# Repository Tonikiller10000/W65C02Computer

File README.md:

# W65C02Computer

### Description:
This is an 8 bit computer made with the W65C02 processor inspired by Ben Eater.
After board arrival, I will test the clk maximum speed (20MHz), some methods to write into ROM (take\`s too much time to write to it) and some other experiments with this design, beeing made mostly after the Ben Eater\`s original design.

### Features:
 - 8 bit processor
 - 1-10MHz CLK
 - 16K RAM
 - 32K ROM
 - USB C Powered
 - Serial interface
 - Multiple GPIO

<table>
  <tr>
    <td></td>
    <td></td>
  </tr>
 </table>

Schematic:  

Datasheets:
- W65C02 (Processor): https://eater.net/datasheets/w65c02s.pdf
- W65C22 (VIA): https://eater.net/datasheets/w65c22.pdf
- AT28C256 (32K x 8 EERPOM): https://ww1.microchip.com/downloads/en/DeviceDoc/doc0006.pdf
- CY7c199  (32K x 8  RAM): https://media.digikey.com/pdf/Data%20Sheets/Cypress%20PDFs/CY7C199.pdf
- R6551 (ACIA): https://pdf.datasheetcatalog.com/datasheets/2300/501026_DS.pdf
- MAX232 (Serial Port Driver): https://www.ti.com/lit/ds/symlink/max232.pdf
- MAX232 (Second datasheet): https://pdf1.alldatasheet.com/datasheet-pdf/view/73113/MAXIM/MAX232EPE.html
- 74HC00 (NAND Gate): https://www.diodes.com/assets/Datasheets/74HC00.pdf

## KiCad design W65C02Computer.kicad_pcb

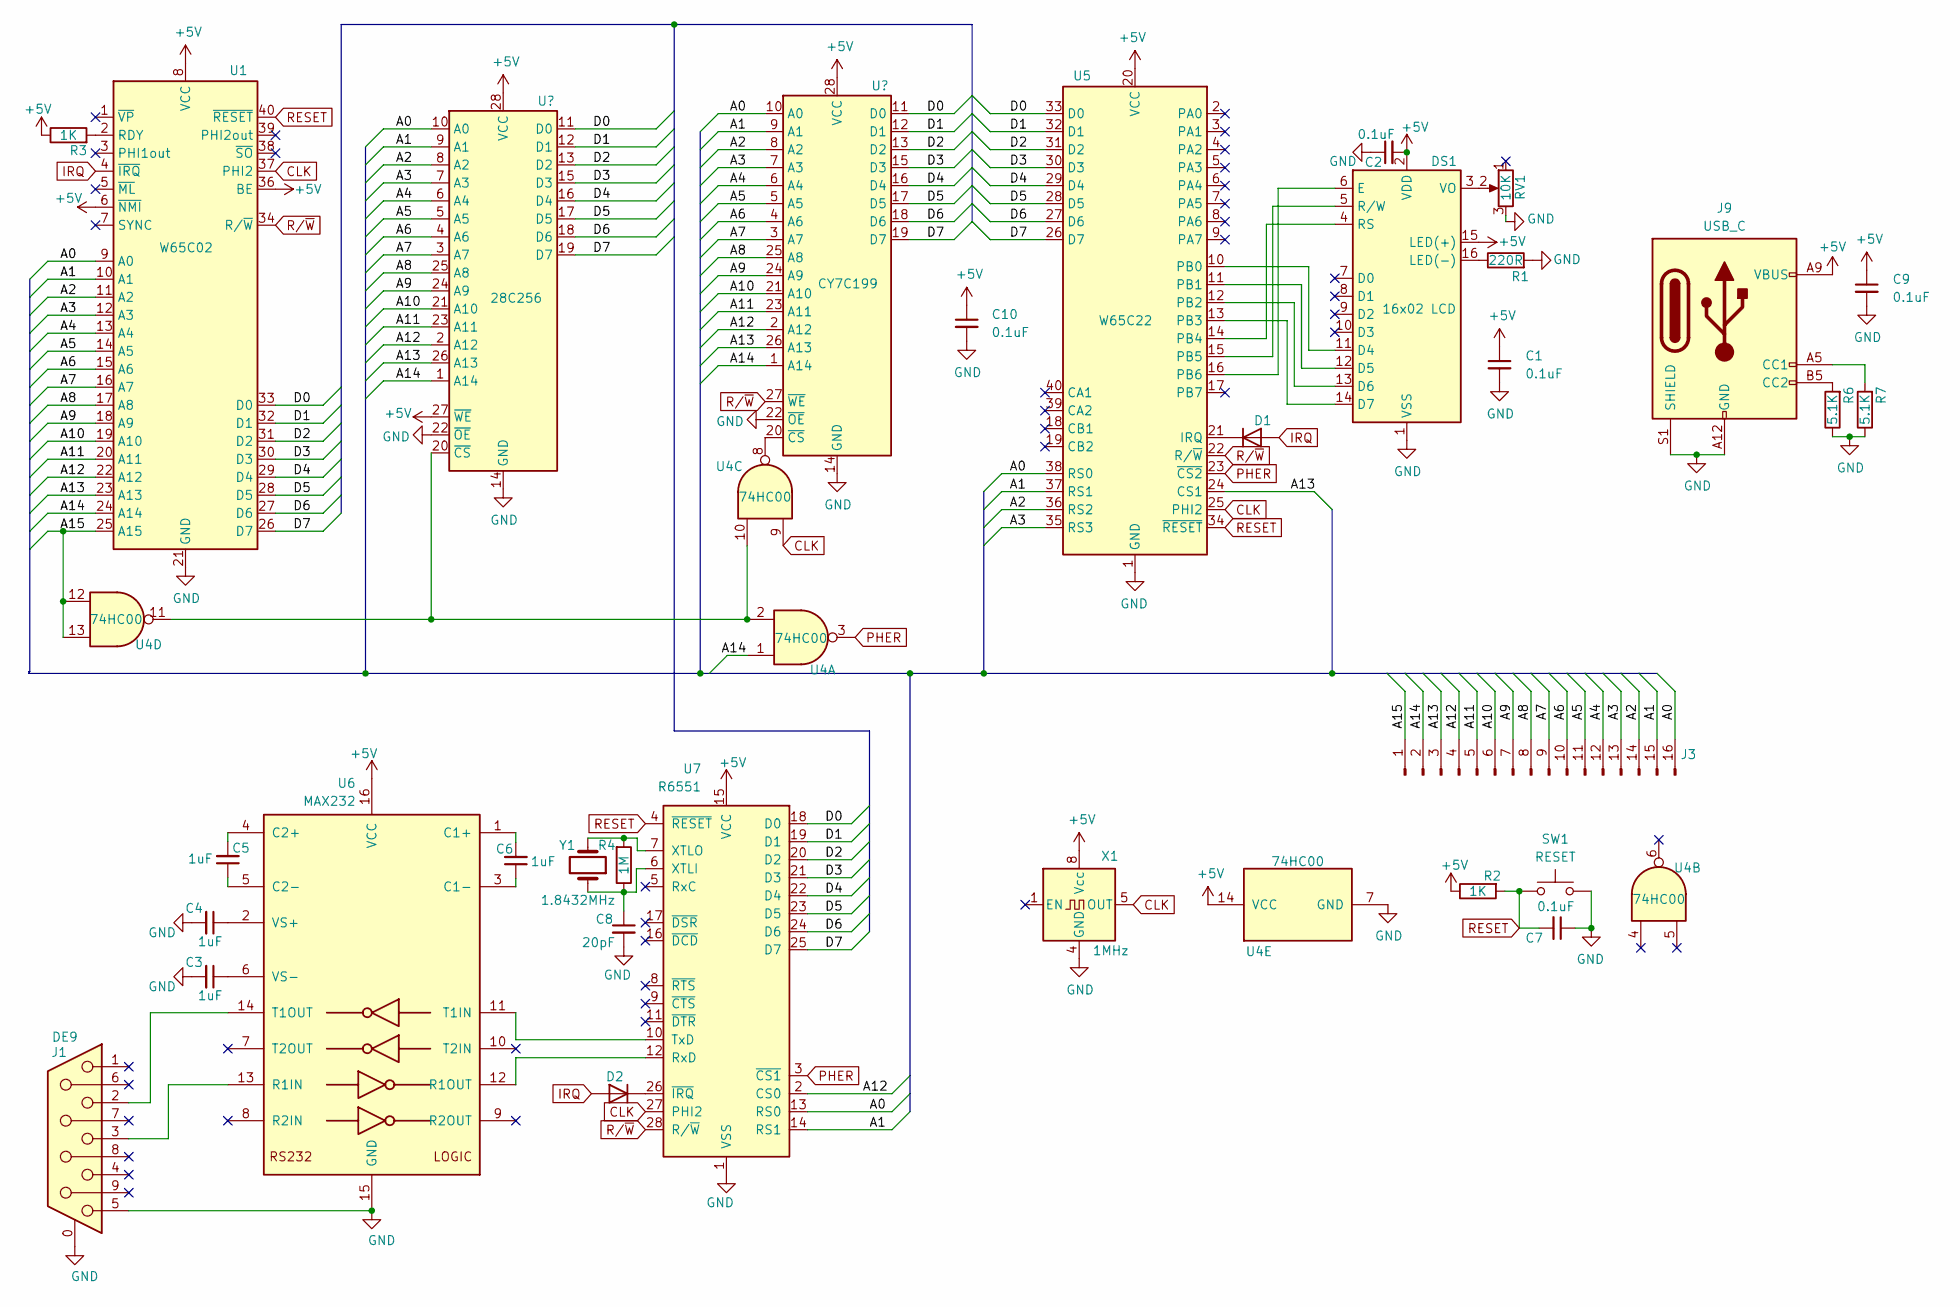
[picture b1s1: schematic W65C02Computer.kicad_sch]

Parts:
C1, C2, C7, C9, C10: 0.1uF; C_0603_1608Metric_Pad1.08x0.95mm_HandSolder
C3, C4, C5, C6: 1uF; C_0603_1608Metric_Pad1.08x0.95mm_HandSolder
C8: 20pF; C_0603_1608Metric_Pad1.08x0.95mm_HandSolder
D1, D2: D; D_MELF
DS1: 16x02 LCD; PinHeader_1x16_P2.54mm_Vertical
J1: DE9; DSUB-9_Female_Horizontal_P2.77x2.84mm_EdgePinOffset7.70mm_H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
J3: Conn_01x16_Pin; PinHeader_1x16_P2.54mm_Vertical
J9: USB_C
R1: 220R; R_0603_1608Metric_Pad0.98x0.95mm_HandSolder
R2, R3: 1K; R_0603_1608Metric_Pad0.98x0.95mm_HandSolder
R4: 1M; R_0603_1608Metric_Pad0.98x0.95mm_HandSolder
R6, R7: 5.1K; R_0603_1608Metric_Pad0.98x0.95mm_HandSolder
RV1: 10K; Potentiometer_Runtron_RM-065_Vertical
SW1: RESET; SW_PUSH_6mm
U1: W65C02; DIP-40_W15.24mm
U2: 28C256; DIP-28_W15.24mm_Socket
U3: CY7C199; DIP-28_W7.62mm_LongPads
U4: 74HC00; DIP-14_W7.62mm_LongPads
U5: W65C22; DIP-40_W15.24mm
U6: MAX232; DIP-16_W7.62mm_LongPads
U7: R6551; DIP-28_W15.24mm
X1: 1MHz; Oscillator_DIP-8
Y1: 1.8432MHz; Crystal_HC50_Horizontal_1EP_style1

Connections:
+5V: C1.1, C2.2, C9.1, C10.1, DS1.2 (VDD), DS1.15 (LED(+)), J9.A9 (VBUS), J9.B9 (VBUS), R2.1, R3.1, U1.6 (~NMI), U1.8 (VCC), U1.36 (BE), U2.27 (~WE), U2.28 (VCC), U3.28 (VCC), U4.14 (VCC), U5.20 (VCC), U6.16 (VCC), U7.15 (VCC), X1.8 (Vcc); also elsewhere on the board
/A0: J3.16, U1.9 (A0), U2.10 (A0), U3.10 (A0), U5.38 (RS0), U7.13 (RS0)
/A1: J3.15, U1.10 (A1), U2.9 (A1), U3.9 (A1), U5.37 (RS1), U7.14 (RS1)
/A2: J3.14, U1.11 (A2), U2.8 (A2), U3.8 (A2), U5.36 (RS2)
/A3: J3.13, U1.12 (A3), U2.7 (A3), U3.7 (A3), U5.35 (RS3)
/A4: J3.12, U1.13 (A4), U2.6 (A4), U3.6 (A4)
/A5: J3.11, U1.14 (A5), U2.5 (A5), U3.5 (A5)
/A6: J3.10, U1.15 (A6), U2.4 (A6), U3.4 (A6)
/A7: J3.9, U1.16 (A7), U2.3 (A7), U3.3 (A7)
/A8: J3.8, U1.17 (A8), U2.25 (A8), U3.25 (A8)
/A9: J3.7, U1.18 (A9), U2.24 (A9), U3.24 (A9)
/A10: J3.6, U1.19 (A10), U2.21 (A10), U3.21 (A10)
/A11: J3.5, U1.20 (A11), U2.23 (A11), U3.23 (A11)
/A12: J3.4, U1.22 (A12), U2.2 (A12), U3.2 (A12), U7.2 (CS0)
/A13: J3.3, U1.23 (A13), U2.26 (A13), U3.26 (A13), U5.24 (CS1)
/A14: J3.2, U1.24 (A14), U2.1 (A14), U3.1 (A14), U4.1
/A15: J3.1, U1.25 (A15), U4.12, U4.13
/D0: U1.33 (D0), U2.11 (D0), U3.11 (D0), U5.33 (D0), U7.18 (D0)
/D1: U1.32 (D1), U2.12 (D1), U3.12 (D1), U5.32 (D1), U7.19 (D1)
/D2: U1.31 (D2), U2.13 (D2), U3.13 (D2), U5.31 (D2), U7.20 (D2)
/D3: U1.30 (D3), U2.15 (D3), U3.15 (D3), U5.30 (D3), U7.21 (D3)
/D4: U1.29 (D4), U2.16 (D4), U3.16 (D4), U5.29 (D4), U7.22 (D4)
/D5: U1.28 (D5), U2.17 (D5), U3.17 (D5), U5.28 (D5), U7.23 (D5)
/D6: U1.27 (D6), U2.18 (D6), U3.18 (D6), U5.27 (D6), U7.24 (D6)
/D7: U1.26 (D7), U2.19 (D7), U3.19 (D7), U5.26 (D7), U7.25 (D7)
CLK: U1.37 (PHI2), U4.9, U5.25 (PHI2), U7.27 (PHI2), X1.5 (OUT)
GND: C1.2, C2.1, C3.2, C4.2, C7.1, C8.2, C9.2, C10.2, DS1.1 (VSS), J1.0 (PAD), J1.5, J9.A12 (GND), J9.B12 (GND), J9.S1 (SHIELD), R1.2, R6.1, R7.1, RV1.3, SW1.1, U1.21 (GND), U2.14 (GND), U2.22 (~OE), U3.14 (GND), U3.22 (~OE), U4.7 (GND), U5.1 (GND), U6.15 (GND), U7.1 (VSS), X1.4 (GND), Y1.3; also elsewhere on the board
IRQ: D1.2 (A), D2.2 (A), U1.4 (~IRQ)
unnamed: D1.1 (K), U5.21 (IRQ)
unnamed: D2.1 (K), U7.26 (~IRQ)
unnamed: DS1.11 (D4), U5.10 (PB0)
unnamed: DS1.12 (D5), U5.11 (PB1)
unnamed: DS1.13 (D6), U5.12 (PB2)
unnamed: DS1.14 (D7), U5.13 (PB3)
unnamed: DS1.6 (E), U5.16 (PB6)
unnamed: DS1.16 (LED(-)), R1.1
unnamed: DS1.4 (RS), U5.14 (PB4)
unnamed: DS1.5 (R/W), U5.15 (PB5)
unnamed: DS1.3 (VO), RV1.2
unnamed: J9.A5 (CC1), R7.2
unnamed: J9.B5 (CC2), R6.2
unnamed: R3.2, U1.2 (RDY)
unnamed: U2.20 (~CS), U4.2, U4.10, U4.11
unnamed: U3.20 (~CS), U4.8
unnamed: C6.2, U6.1 (C1+)
unnamed: C6.1, U6.3 (C1-)
unnamed: C5.2, U6.4 (C2+)
unnamed: C5.1, U6.5 (C2-)
unnamed: J1.3, U6.13 (R1IN)
unnamed: U6.12 (R1OUT), U7.12 (RxD)
unnamed: U6.11 (T1IN), U7.10 (TxD)
unnamed: J1.2, U6.14 (T1OUT)
unnamed: C4.1, U6.2 (VS+)
unnamed: C3.1, U6.6 (VS-)
unnamed: C8.1, R4.1, U7.6 (XTLI), Y1.1
unnamed: R4.2, U7.7 (XTLO), Y1.2
PHER: U4.3, U5.23 (~CS2), U7.3 (~CS1)
RESET: C7.2, R2.2, SW1.2, U1.40 (~RESET), U5.34 (~RESET), U7.4 (~RESET)
R/~W: U1.34 (R/~W), U3.27 (~WE), U5.22 (R/~W), U7.28 (R/~W)

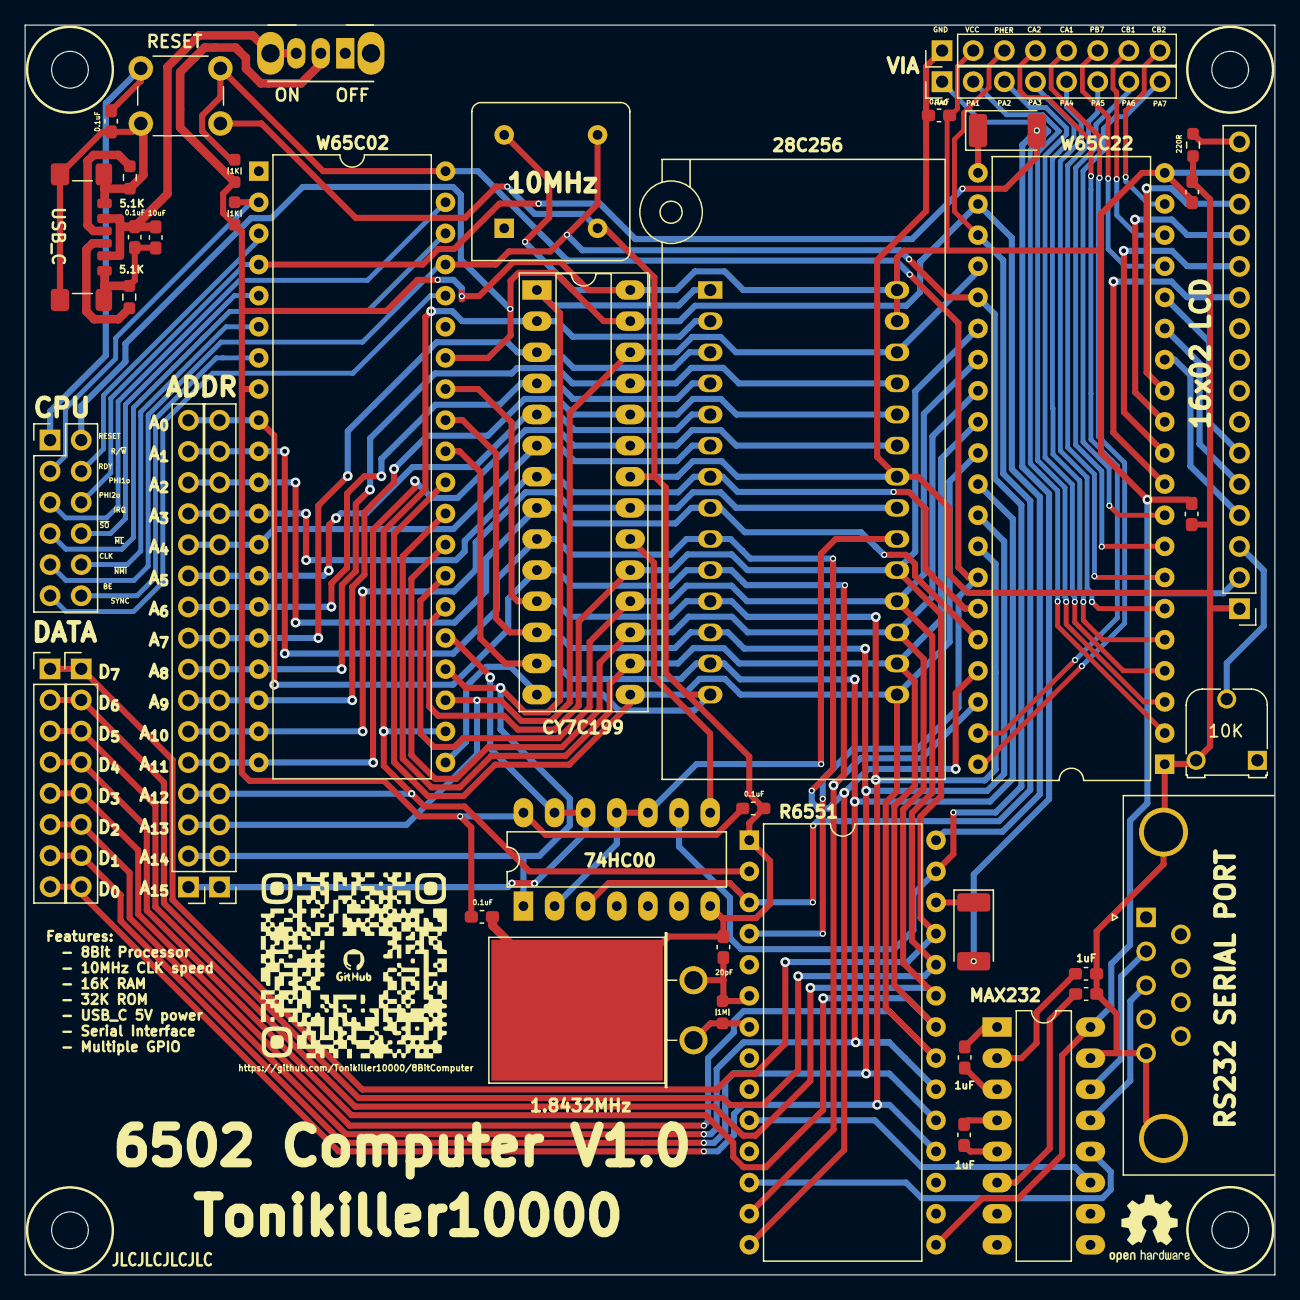
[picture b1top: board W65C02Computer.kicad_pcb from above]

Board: 2 copper layers, 102.0 x 102.0 mm, 37 parts (0 on the bottom side), 59 nets.

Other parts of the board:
C9#2, C9#3: 0.1uF; C_0603_1608Metric_Pad1.08x0.95mm_HandSolder
C9#4: 10uF; C_0603_1608Metric_Pad1.08x0.95mm_HandSolder
SW2: SW_SPDT; SW_CuK_OS102011MA1QN1_SPDT_Angled

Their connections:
+5V: C9#3.1; also elsewhere on the board
GND: C9#3.2; also elsewhere on the board

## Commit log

2024-02-24 upd1
